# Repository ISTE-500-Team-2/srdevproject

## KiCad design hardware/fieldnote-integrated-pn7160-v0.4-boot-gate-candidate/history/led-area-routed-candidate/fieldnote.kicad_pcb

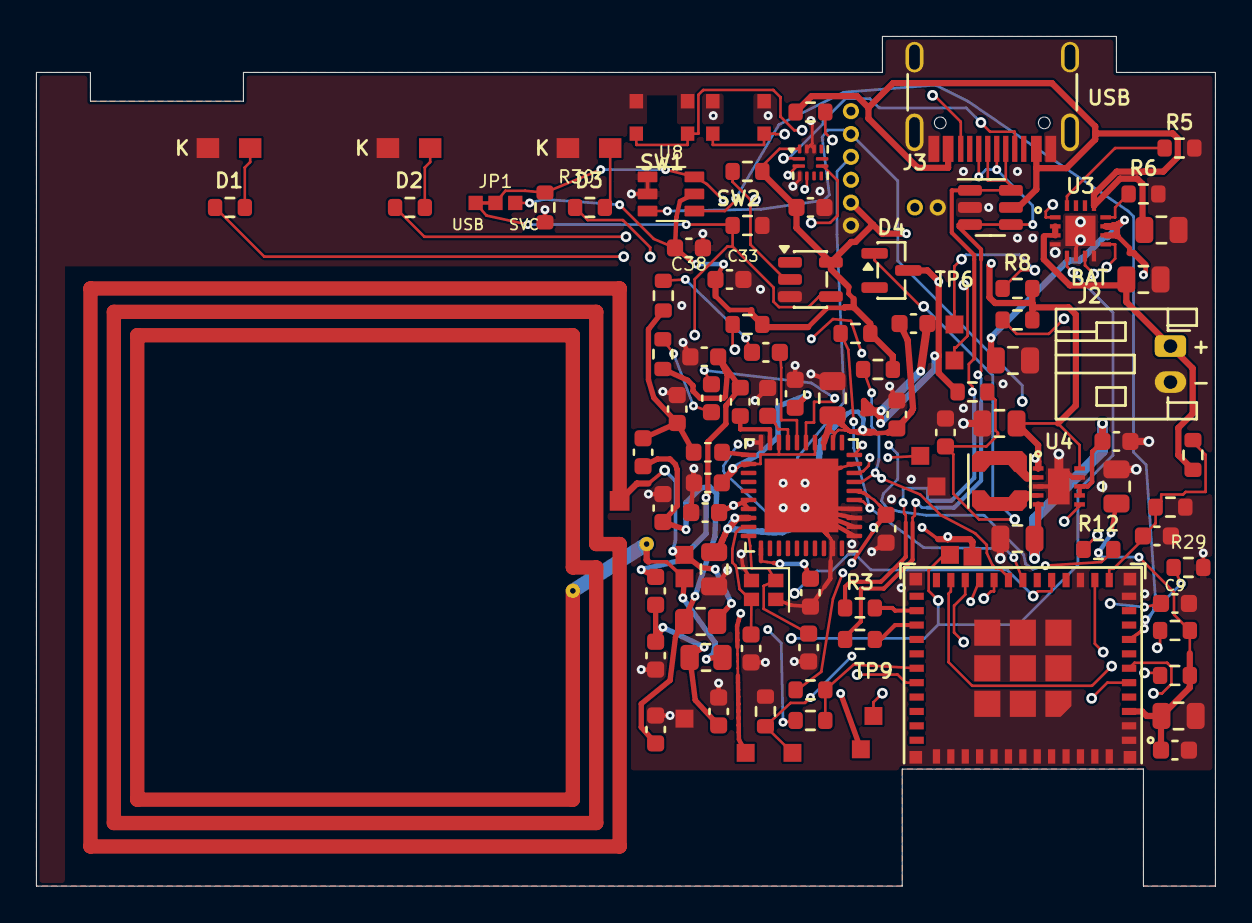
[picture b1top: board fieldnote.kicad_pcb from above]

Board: 4 copper layers, 65.5 x 47.2 mm, 104 parts (0 on the bottom side), 60 nets.

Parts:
ANT1: 3-turn PCB NFC loop; NFC_Loop
C1, C12, C14: 4.7uF 16V X5R; C_0805
C2, C10: 10uF 16V X5R; C_0805
C3, C4, C6, C7: 22uF 10V X5R; C_0805
C5, C8, C11, C13, C30, C32, C33, C38: 100nF 50V X7R; C_0603
C9, C36: 1uF 16V X7R; C_0603
C15, C16, C17, C18: 2.2uF 10V X7R 10%; C_0603
C19: 1uF 16V X7R 10%; C_0603
C22, C23: 13pF C0G 50V 1%; C_0603
C24, C25: 330pF C0G 50V 2%; C_0603
C26, C27: 130pF C0G 50V 2%; C_0603
C28, C29: 300pF C0G 50V 2%; C_0603
C31, C37: 1nF X7R 50V 5%; C_0603
C34, C35: 47pF C0G 50V; C_0603
D1: GREEN LED; LED_0805
D2: AMBER LED; LED_0805
D3: RED LED; LED_0805
D4: BAV199-7-F; SOT23
FB1: 600R@100MHz 500mA; C_0603
J1: USB-C USB 2.0; USB_C
J2: 1S protected LiPo; JST_PH
J3: CELL NTC 10k; Header_1x02
J4: UART recovery; Header_1x06
JP1: USB / SERVICE PERMIT; Permit_Selector_3_Bridged12
L1, L2: 160nH 5%; L_0603
L3: 1.5uH 20%; Coilcraft_LPS3015
R1: 887k 1%; R_0603
R2: 10k 1%; R_0603
R3, R4: 22R; R_0603
R5: 8.66k 1%; R_0603
R6: 1.62k 1%; R_0603
R7, R8, R9, R13, R14, R15: 10k; R_0603
R10: 220k 1%; R_0603
R11, R19: 100k 1%; R_0603
R12, R29, R30: 47k 1%; R_0603
R16, R17, R18: 1k; R_0603
R20, R21: 4.7k; R_0603
R22, R23: 1.3R 1% 0.5W; R_0805
R24, R25: 2.2k 1%; R_0603
R26: 150k 1%; R_0603
R27: 0R IRQ SERVICE LINK; R_0603
R28: 0R UART SERVICE LINK; R_0603
SW1: RESET; TL3701
SW2: BOOT; TL3701
TP1: 3V3; TestPoint
TP2: PN_1V8; TestPoint
TP3: NFC_IRQ; TestPoint
TP4: PN_TX_LDO; TestPoint
TP5: NFC_VEN; TestPoint
TP6: CHG_N; TestPoint
TP7: PGOOD_N; TestPoint
TP8, TP13: GND; TestPoint
TP9: USB_LIMITED; TestPoint
TP10: USB_HIGH_CURRENT; TestPoint
TP11: ANT_A; TestPoint
TP12: ANT_B; TestPoint
U1: ESP32-C3-MINI-1-N4X; ESP32-C3-MINI-1
U2: PN7160A1HN/C100E; PN7160_HVQFN40
U3: BQ24074RGTR; BQ24074_RGT16
U4: TPS63031DSKR; TPS63031_DSK10
U5: USBLC6-2SC6; SOT23-6
U6: TUSB320LAIRWBR; TUSB320_RWB12
U7: SN74LVC1G04DBVR; SOT23-5
U8: SN74LVC1G97DBVR; TI_DBV0006A
Y1: 27.12MHz CL10pF; Crystal_2016

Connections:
3V3: C6.1, C7.1, C10.1, C11.1, C19.1, C32.1, C33.1, C38.1, J4.2 (3V3), JP1.3 (SERVICE_3V3), R7.2, R8.2, R9.2, R13.2, R14.2, R15.2, R20.2, R21.2, TP1.1 (3V3), U1.3 (3V3), U2.6 (VDD_PAD), U4.1 (VOUT), U4.10 (FB), U6.12 (VDD), U7.5 (VCC), U8.5 (VCC)
ANT_A: ANT1.1 (A), R22.2, TP11.1 (ANT_A)
ANT_B: ANT1.2 (B), R23.2, TP12.1 (ANT_B)
BAT: C2.1, J2.1 (BAT+), R10.1, U3.2 (BAT), U3.3 (BAT)
BAT_ADC: C8.1, R10.2, R11.1, U1.12 (IO0)
BAT_TS: J3.1 (TS), U3.1 (TS)
BOOT_IO2: R13.1, U1.5 (IO2)
BOOT_IO8: R14.1, U1.22 (IO8)
BOOT_IO9: J4.6 (BOOT), R15.1, SW2.1 (IO9), SW2.2 (IO9), U1.23 (IO9)
CC1: J1.A5, U6.1 (CC1)
CC2: J1.B5, U6.2 (CC2)
CHG_ILIM: R6.1, U3.12 (ILIM)
CHG_ISET: R5.1, U3.16 (ISET)
CHG_N: R8.1, TP6.1 (CHG_N), U3.9 (CHG_N)
D1_ANODE: D1.2 (A), R16.2
D2_ANODE: D2.2 (A), R17.2
D3_ANODE: D3.2 (A), R18.2
ESP_EN: R29.1, U1.8 (EN), U8.4 (Y_CHIP_EN)
ESP_RESET_RC: C9.1, J4.5 (RESET_RC), R12.1, SW1.1 (RESET_RC), SW1.2 (RESET_RC), U8.3 (In0_RESET_RC)
GND: C1.2, C2.2, C3.2, C4.2, C5.2, C6.2, C7.2, C8.2, C9.2, C10.2, C11.2, C12.2, C13.2, C14.2, C15.2, C16.2, C17.2, C18.2, C19.2, C22.2, C23.2, C24.2, C25.2, C28.2, C29.2, C30.2, C32.2, C33.2, C34.2, C35.2, C36.2, C38.2, D1.1 (K), D2.1 (K), D3.1 (K), J1.A1, J1.A12, J1.B1, J1.B12, J1.S1, J2.2 (GND), J3.2 (GND), J4.1 (GND), R2.2, R5.2, R6.2, R11.2, R19.2, R29.2, R30.2, SW1.3 (GND), SW1.4 (GND), SW2.3 (GND), SW2.4 (GND), TP8.1 (GND), TP13.1 (GND), U1.1 (GND), U1.2 (GND), U1.11 (GND), U1.14 (GND), U1.36 (GND), U1.37 (GND), U1.38 (GND), U1.39 (GND), U1.40 (GND), U1.41 (GND), U1.42 (GND), U1.43 (GND), U1.44 (GND), U1.45 (GND), U1.46 (GND), U1.47 (GND), U1.48 (GND), U1.49 (GND), U1.50 (GND), U1.51 (GND), U1.52 (GND), U1.53 (GND), U2.1 (I2C_ADR0), U2.2 (DWL_REQ), U2.3 (I2C_ADR1), U2.4 (VSS_PAD), U2.9 (VSS_A), U2.20 (VSS_TX), U2.39 (WKUP_REQ), U2.41 (EP), U3.4 (CE_N), U3.6 (EN1), U3.8 (VSS), U3.17 (EP), U4.3 (PGND), U4.9 (GND), U4.11 (EP), U5.2 (GND), U6.3 (PORT), U6.10 (GND), U6.11 (EN_N), U7.3 (GND), U8.1 (In1), U8.2 (GND), Y1.2 (CASE), Y1.4 (CASE)
LED_AMBER: R17.1, U1.6 (IO3)
LED_GREEN: R16.1, U1.13 (IO1)
LED_RED: R18.1, U1.16 (IO10)
MCU_NFC_IRQ: R27.2, R28.2, U1.30 (RXD0)
MCU_USB_DM: R3.2, U1.26 (IO18_USB_DM)
MCU_USB_DP: R4.2, U1.27 (IO19_USB_DP)
NFC_IRQ: R27.1, TP3.1 (NFC_IRQ), U2.8 (IRQ)
NFC_OSCIN: C22.1, U2.30 (NFC_CLK_XTAL1), Y1.1 (XTAL1)
NFC_OSCOUT: C23.1, U2.29 (XTAL2), Y1.3 (XTAL2)
NFC_RXN: C37.2, U2.15 (RXN)
NFC_RXP: C31.2, U2.16 (RXP)
NFC_SCL: R21.1, U1.19 (IO5), U2.7 (I2C_SCL)
NFC_SDA: R20.1, U1.18 (IO4), U2.5 (I2C_SDA)
NFC_TX1: L1.1, U2.21 (TX1)
NFC_TX2: L2.1, U2.19 (TX2)
NFC_VBAT: C12.1, C13.1, C14.1, FB1.2, U2.12 (VBAT2), U2.13 (VDD_UP), U2.28 (VBAT)
NFC_VEN: R19.1, TP5.1 (NFC_VEN), U1.21 (IO7), U2.10 (VEN)
NFC_VMID: C30.1, U2.17 (VDD_VMID)
PGOOD_N: R9.1, TP7.1 (PGOOD_N), U3.7 (PGOOD_N)
PN_1V8: C15.1, C16.1, TP2.1 (PN_1V8), U2.26 (VDD_A), U2.27 (VDD), U2.31 (VDD_D)
PN_TX_LDO: C17.1, C18.1, TP4.1 (PN_TX_LDO), U2.14 (VDD_TX), U2.18 (TVDD_IN), U2.22 (TVDD_IN2)
POWER_PERMIT: JP1.2 (COMMON_PERMIT), R12.2, R30.1, U8.6 (In2_POWER_PERMIT)
RF1_FILTER: C24.1, C26.1, L1.2, R24.1
RF1_MATCH: C26.2, C28.1, C34.1, R22.1
RF2_FILTER: C25.1, C27.1, L2.2, R25.1
RF2_MATCH: C27.2, C29.1, C35.1, R23.1
RF_RXN_COUPLED: C37.1, R25.2
RF_RXP_COUPLED: C31.1, R24.2
SW_L1: L3.1, U4.4 (L1)
SW_L2: L3.2, U4.2 (L2)
TPS_EN: C36.1, D4.1 (A1), R26.2, U4.6 (EN)
UART_RX: J4.4 (RX), R28.1
UART_TX: J4.3 (TX), U1.31 (TXD0)
USB_DM: J1.A7, J1.B7, R3.1, U5.1 (DM), U5.6 (DM)
USB_DP: J1.A6, J1.B6, R4.1, U5.3 (DP), U5.4 (DP)
USB_HIGH_CURRENT: JP1.1 (USB_HIGH_CURRENT), R2.1, TP10.1 (USB_HIGH_CURRENT), U3.5 (EN2), U7.4 (Y)
USB_LIMITED: R7.1, TP9.1 (USB_LIMITED), U1.20 (IO6), U6.7 (OUT1), U7.2 (A)
USB_VBUS_DET: R1.2, U6.4 (VBUS_DET)
VBUS: C1.1, J1.A4, J1.A9, J1.B4, J1.B9, R1.1, U3.13 (IN), U5.5 (VBUS)
VSYS: C3.1, C4.1, C5.1, D4.3 (K1_A2), FB1.1, R26.1, U3.10 (OUT), U3.11 (OUT), U4.5 (VIN), U4.7 (PS_SYNC), U4.8 (VINA)
